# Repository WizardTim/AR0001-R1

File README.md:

# AR0001-R1
PCB design files for a simple 3/4" binding post to USB type A adapter.

### Related Videos
* _**'PSU 3/4" Binding Post to USB A Adapter Assembly'**_: [https://youtu.be/g8ivYxvZa-0](https://youtu.be/g8ivYxvZa-0) walkthrough of assembly.

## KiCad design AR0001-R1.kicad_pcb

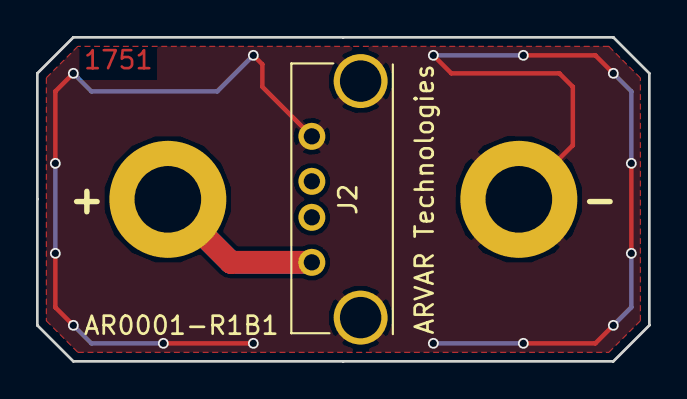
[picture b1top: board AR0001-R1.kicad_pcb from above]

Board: 2 copper layers, 34.0 x 18.0 mm, 3 parts (0 on the bottom side), 2 nets.

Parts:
J1, J3: CONN_01X01_MALE; Banana_Jack_1Pin
J2: USB_A

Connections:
+5V: J1.1, J2.1
GND: J2.4, J2.5, J3.1

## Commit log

2019-01-28 Uploaded existing project files
2020-08-31 Improve readme
2020-08-31 Add hyperlink
2021-04-05 Fix Typo
